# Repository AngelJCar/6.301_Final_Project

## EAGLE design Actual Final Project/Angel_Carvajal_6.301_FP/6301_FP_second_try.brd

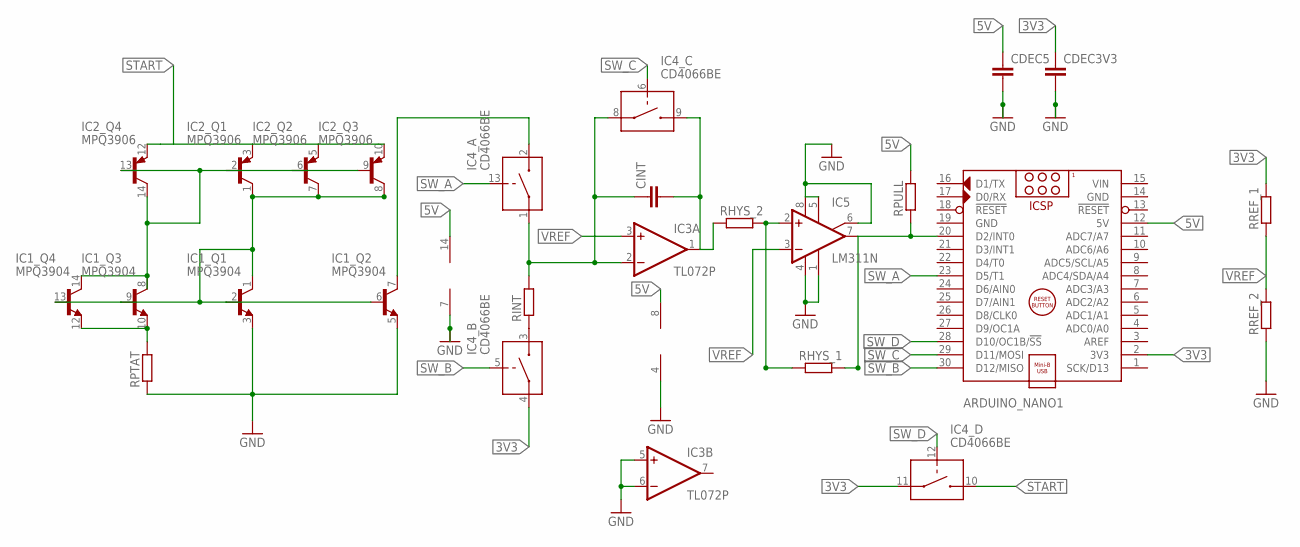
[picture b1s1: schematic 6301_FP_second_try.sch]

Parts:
ARDUINO_NANO1: ARDUINO_NANO
CDEC3V3, CDEC5: C-EU025-024X044; C025-024X044
CINT: C-EU025-024X044; C025-024X044
IC1: MPQ3904; DIL14
IC2: MPQ3906; DIL14
IC3: TL072P; DIL08
IC4: CD4066BE; DIL14
IC5: LM311N; DIL08
RHYS_1, RHYS_2: R-EU_0204/7; 0204/7
RINT: R-EU_0204/7; 0204/7
RPTAT: R-EU_0204/7; 0204/7
RPULL: R-EU_0204/7; 0204/7
RREF_1, RREF_2: R-EU_0204/7; 0204/7

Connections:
3V3: ARDUINO_NANO1.2 (3V3), CDEC3V3.1, IC4.4 (IN/OUT1), IC4.11 (IN/OUT1), RREF_1.2
5V: ARDUINO_NANO1.12 (5V), CDEC5.1, IC3.8 (V+), IC4.14 (V+), RPULL.2
GND: ARDUINO_NANO1.14 (GND), ARDUINO_NANO1.19 (GND), CDEC3V3.2, CDEC5.2, IC1.3 (E), IC1.5 (E), IC3.4 (V-), IC3.5 (+IN), IC3.6 (-IN), IC4.7 (V-), IC5.1 (GND), IC5.4 (V-), IC5.5 (ON), IC5.6 (ON/STR), IC5.8 (V+), RPTAT.1, RREF_2.1
unnamed: IC4.3 (IN/OUT2), RINT.1
unnamed: IC1.10 (E), IC1.12 (E), RPTAT.2
unnamed: IC1.8 (C), IC1.14 (C), IC2.2 (B), IC2.6 (B), IC2.9 (B), IC2.13 (B), IC2.14 (C)
unnamed: ARDUINO_NANO1.20 (D2/INT0), IC5.7 (OUT), RHYS_1.2, RPULL.1
unnamed: IC1.1 (C), IC1.2 (B), IC1.6 (B), IC1.9 (B), IC1.13 (B), IC2.1 (C), IC2.7 (C), IC2.8 (C)
unnamed: CINT.2, IC3.1 (OUT), IC4.9 (IN/OUT2), RHYS_2.1
unnamed: IC1.7 (C), IC4.2 (IN/OUT2)
unnamed: CINT.1, IC3.2 (-IN), IC4.1 (IN/OUT1), IC4.8 (IN/OUT1), RINT.2
START: IC2.3 (E), IC2.5 (E), IC2.10 (E), IC2.12 (E), IC4.10 (IN/OUT2)
SW_A: ARDUINO_NANO1.23 (D5/T1), IC4.13 (CONTROL)
SW_B: ARDUINO_NANO1.30 (D12/MISO), IC4.5 (CONTROL)
SW_C: ARDUINO_NANO1.29 (D11/MOSI), IC4.6 (CONTROL)
SW_D: ARDUINO_NANO1.28 (D10/OC1B/!SS), IC4.12 (CONTROL)
VIN: ARDUINO_NANO1.15 (VIN)
VREF: IC3.3 (+IN), IC5.2 (+IN), IC5.3 (-IN), RHYS_1.1, RHYS_2.2, RREF_1.1, RREF_2.2

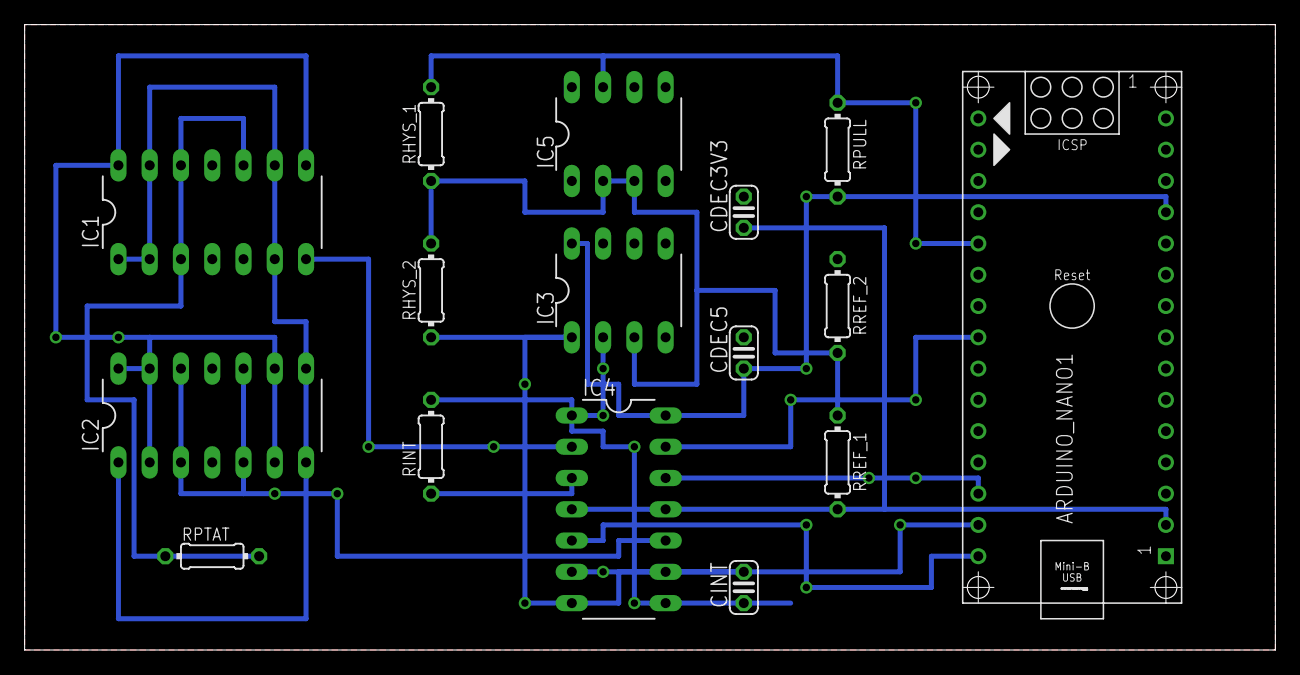
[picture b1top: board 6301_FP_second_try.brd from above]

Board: 2 copper layers, 101.6 x 50.8 mm, 16 parts (0 on the bottom side), 17 nets.

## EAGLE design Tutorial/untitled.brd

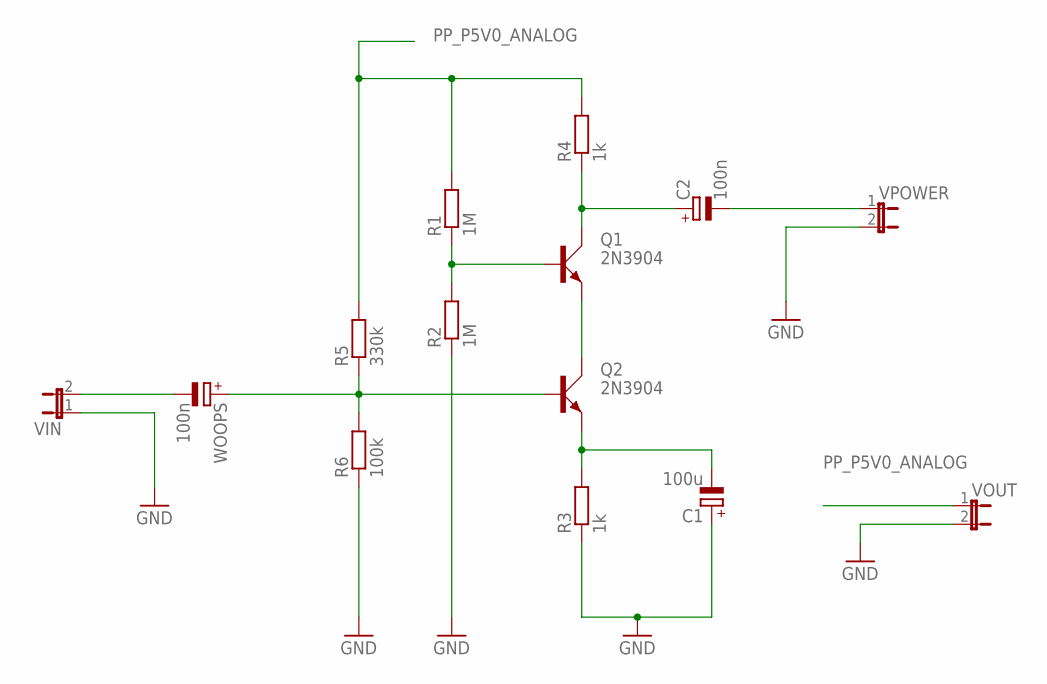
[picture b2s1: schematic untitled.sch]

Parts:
C1: 100u; E5-10,5
C2: 100n; EB25D
Q1, Q2: 2N3904; TO92D
R1, R2: 1M; 0207/10
R3, R4: 1k; 0207/10
R5: 330k; 0207/10
R6: 100k; 0207/10
VIN: JP1E; JP1
VOUT: JP1E; JP1
VPOWER: JP1E; JP1
WOOPS: 100n; E3,5-10

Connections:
GND: C1.+, R2.1, R3.1, R6.1, VIN.1, VOUT.2, VPOWER.2
unnamed: Q1.E, Q2.C
unnamed: C2.+, Q1.C, R4.1
unnamed: Q1.B, R1.1, R2.2
unnamed: VIN.2, WOOPS.-
unnamed: Q2.B, R5.1, R6.2, WOOPS.+
unnamed: C1.-, Q2.E, R3.2
unnamed: C2.-, VPOWER.1
PP_P5V0_ANALOG: R1.2, R4.2, R5.2, VOUT.1

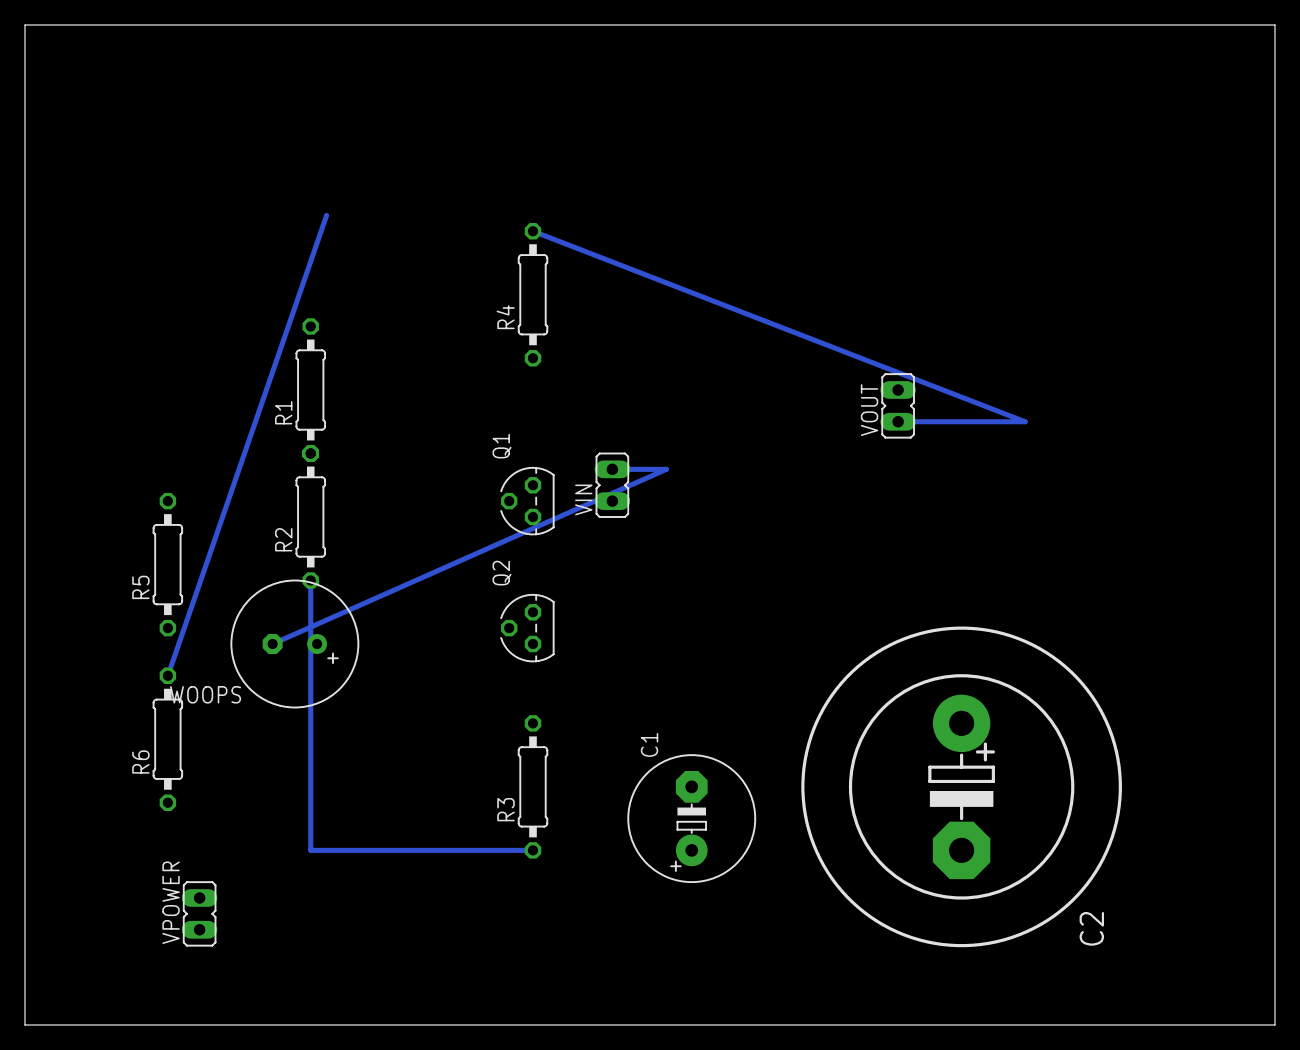
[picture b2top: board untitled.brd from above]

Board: 2 copper layers, 100.0 x 80.0 mm, 14 parts (0 on the bottom side), 9 nets.

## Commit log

2016-12-07 PCB1 Done
2016-12-07 PCB2 Done
    -errors on DRC (vias, and something with micro-controller)
2016-12-08 PCB3_DONE
    -Still get errors from DRC: Dimension from Arduino/Via Drill sizes
    -Got the 2nd Layer in though
